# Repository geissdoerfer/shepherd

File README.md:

# SHEpHERD: SyncHronized Energy Harvesting Emulator RecorDer

DEPRECATION NOTICE:
This repository has been deprecated in favor of [the next generation of Shepherd](https://github.com/orgua/shepherd).

Batteryless sensor nodes depend on harvesting energy from their environment.
Developing solutions involving groups of batteryless nodes requires a tool to analyze, understand and replicate spatio-temporal harvesting conditions.
*shepherd* is a testbed for the batteryless Internet of Things, allowing to record harvesting conditions at multiple points in space over time.
The recorded data can be replayed to attached wireless sensor nodes, examining their behaviour under the constraints of spatio-temporal energy availability.

**Features**

 - High-speed, high resolution current and voltage sensing
 - Technology-agnostic: Currently, solar and kinetic energy harvesting are supported
 - Remote programming/debugging of ARM Cortex-M MCUs using Serial-Wire-Debug
 - High resolution, synchronized GPIO tracing
 - Configurable, constant voltage power supply for attached sensor nodes
 - Level-translated serial connection to the attached sensor nodes

For a detailed description see our [Paper](https://wwwpub.zih.tu-dresden.de/~mzimmerl/pubs/geissdoerfer19shepherd.pdf).

A *shepherd* instance consists of a group of spatially distributed *shepherd* nodes that are time-synchronized with each other.
Each *shepherd* node consists of a [BeagleBone](https://beagleboard.org/bone), the *shepherd* cape and a particular choice of capelets according to the user requirements.

This repository contains the hardware design files for the shepherd cape and the various capelets, the software running on each *shepherd* node as well as the tool to orchestrate a group of *shepherd* nodes connected to a network.

## Quickstart

Start by assembling your *shepherd* nodes, consisting of a BeagleBone Green/Black, a *shepherd* cape, a harvesting capelet and a target capelet.
The next step is to manually install the latest Ubuntu Linux on each BeagleBone.
You can install it to SD-card or the on-board EMMC flash, following [the official instructions](https://elinux.org/BeagleBoardUbuntu).
Make sure to follow the instructions for **BeagleBone**.

The following instructions describe how to install the *shepherd* software on a group of *shepherd* nodes connected to an Ethernet network.
We assume that your local machine is connected to the same network, that the nodes have internet access and that you know the IP address of each node.

If you haven't done it yet, clone this repository to your local machine:

```
git clone https://github.com/geissdoerfer/shepherd.git
```

Next, install the tools used for installing and controlling the *shepherd* nodes.
We'll use [Ansible](https://www.ansible.com/) to remotely roll out the basic configuration to each *shepherd* node and *shepherd-herd* to orchestrate recording/emulation across all nodes.
The tools are hosted on `PyPI` and require Python version >= 3.6.
You'll also need to have `sshpass` installed on your machine, which is available through the package management system of all major distributions.
Install the tools using `pip`:

```
pip3 install ansible shepherd-herd
```

The `inventory/herd.yml` file shows an example of how to provide the host names and known IP addresses of your BeagleBones.
Adjust it to reflect your setup.
You can arbitrarily choose and assign the hostnames (sheep0, sheep1, in this example) and the ansible_user (jane in this example).

```
sheep:
  hosts:
    sheep0:
        ansible_host: 192.168.1.100
    sheep1:
        ansible_host: 192.168.1.101
    sheep2:
        ansible_host: 192.168.1.102
  vars:
    ansible_user: jane
```

Now run the `bootstrap.yml` *Ansible* playbook, which sets the hostname, creates a user and enables passwordless ssh and sudo:

```
ansible-playbook deploy/bootstrap.yml
```

Finally, use the `install.yml` playbook to setup the *shepherd* software, optionally configuring PTP for time-synchronization:

```
ansible-playbook deploy/install.yml -e ptp=true
```

## Usage

Record two minutes of data:

```
shepherd-herd record -l 120 -o recording.h5
```
The command starts the recording asynchronously and returns after all nodes have started recording.
While the nodes are still recording (indicated by blinking of LED 1 and 2), prepare a directory on your local machine:

```
mkdir ~/shepherd_recordings
```

After the nodes stop blinking, you can retrieve the data to analyze it on your local machine:

```
shepherd-herd retrieve recording.h5 ~/shepherd_recordings
```

After installing some additional dependencies, you can use the provided command line utility from `extra/plot.py` to visualize the recorded data:

```
pip install numpy matplotlib h5py click
python extra/plot.py -f ~/shepherd_recordings/sheep1/rec.h5
```

For a detailed description of the [HDF5](https://en.wikipedia.org/wiki/Hierarchical_Data_Format) based data format, refer to the [corresponding documentation](https://shepherd-testbed.readthedocs.io/en/latest/user/data_format.html).

Finally, replay the previously recorded data to the attached sensor nodes, recording their power consumption:

```
shepherd-herd emulate -o consumption.h5 recording.h5
```

Try `shepherd-herd --help` or check out the documentation [here](https://shepherd-testbed.readthedocs.io/en/latest/user/cli.html#shepherd-herd) for a list of all options.

## Problems and Questions

*shepherd* is an early stage project and chances are that something is not working as expected.
Also, some features are not yet fully supported or documented.
If you experience issues or require additional features, please get in touch via e-mail or by creating an issue on github.

## Documentation

The documentation is hosted on [readthedocs](https://shepherd-testbed.readthedocs.io/en/latest/).

## People

*shepherd* development is lead at the Networked Embedded Systems Lab at TU Dresden as part of the DFG-funded project Next-IoT.

The following people have contributed to *shepherd*:

 - [Kai Geissdoerfer](https://www.researchgate.net/profile/Kai_Geissdoerfer)
 - [Mikolaj Chwalisz](https://www.tkn.tu-berlin.de/team/chwalisz/)
 - [Marco Zimmerling](https://wwwpub.zih.tu-dresden.de/~mzimmerl/)
 - [Justus Paulick](https://github.com/kugelbit)
 - [Boris Blokland](https://github.com/borro0)
 - [Ingmar Splitt](https://github.com/orgua)

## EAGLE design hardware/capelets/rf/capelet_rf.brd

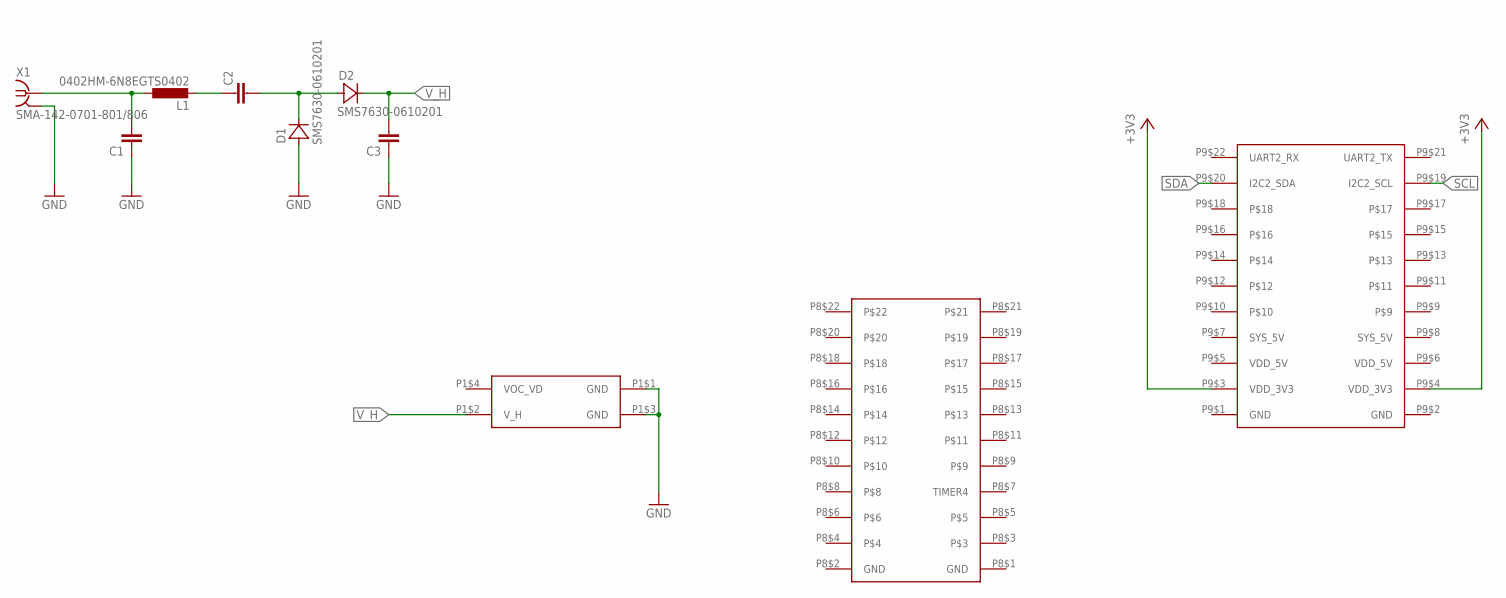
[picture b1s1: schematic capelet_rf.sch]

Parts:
C1, C2, C3: C_SMD0402; CAPC1005X55
D1, D2: SMS7630-0610201; DIOC0502X27N
L1: 0402HM-6N8EGTS0402; INDC1004X60N
X1: SMA-142-0701-801/806; J502-ND-142-0701-801/806
Y1: SHPRD_CPLT_H

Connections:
+3V3: Y1.P9$3 (VDD_3V3), Y1.P9$4 (VDD_3V3)
GND: C1.1, C3.1, D1.1 (A), X1.G@1 (2), X1.G@2 (2), X1.G@3 (2), X1.G@4 (2), Y1.P1$1 (GND), Y1.P1$3 (GND), Y1.P8$1 (GND), Y1.P8$2 (GND), Y1.P9$1 (GND), Y1.P9$2 (GND)
unnamed: C2.2, D1.2 (C), D2.1 (A)
unnamed: C1.2, L1.1, X1.1
unnamed: C2.1, L1.2
SCL: Y1.P9$19 (I2C2_SCL)
SDA: Y1.P9$20 (I2C2_SDA)
SYS_5V: Y1.P9$7 (SYS_5V), Y1.P9$8 (SYS_5V)
VDD_5V: Y1.P9$5 (VDD_5V), Y1.P9$6 (VDD_5V)
V_H: C3.2, D2.2 (C), Y1.P1$2 (V_H)

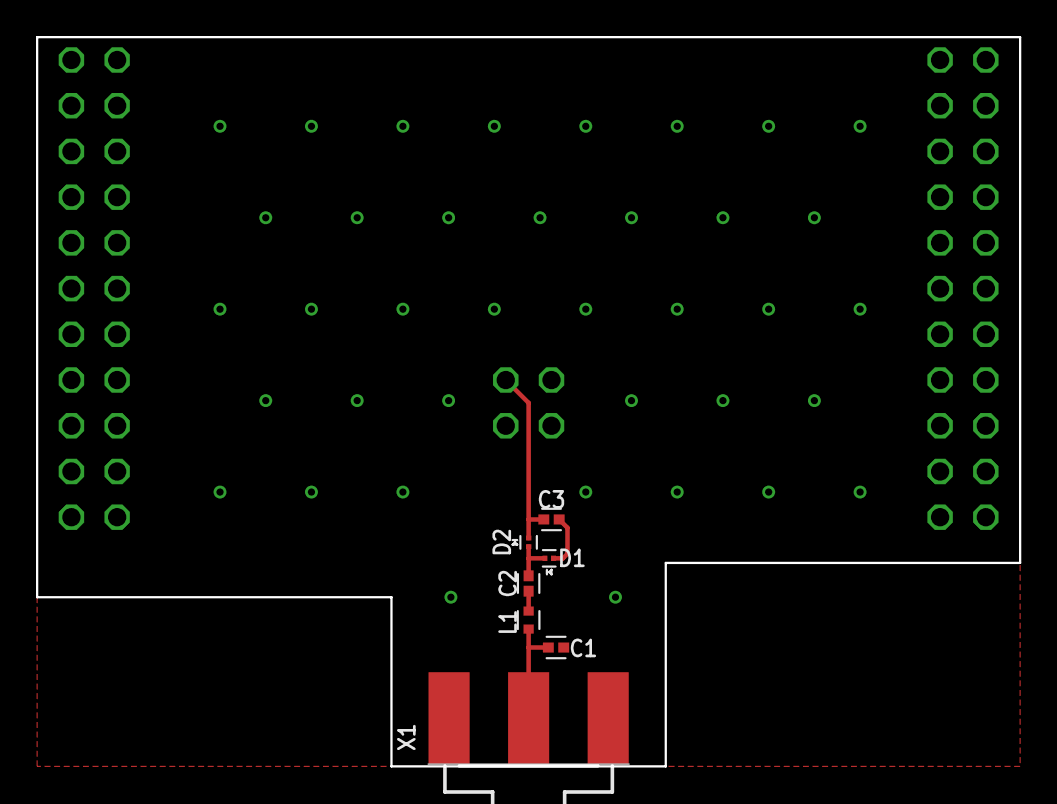
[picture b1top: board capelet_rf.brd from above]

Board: 2 copper layers, 54.6 x 40.5 mm, 8 parts (0 on the bottom side), 8 nets.

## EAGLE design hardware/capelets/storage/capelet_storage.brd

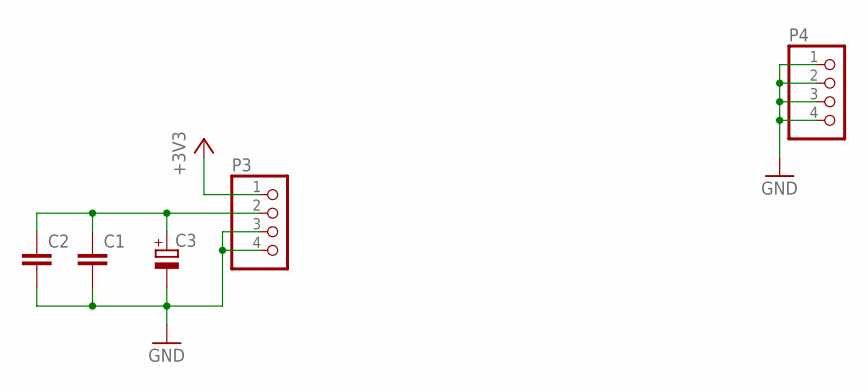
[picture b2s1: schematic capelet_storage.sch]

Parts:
C1: C_SMD0805; CAPC2012X145
C2: C_SMD1210; CAPC3225X280
C3: CPOL-EUE5-8.5; E5-8,5
P3, P4: PINHD-1X4; 1X04

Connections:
+3V3: P3.1
GND: C1.2, C2.2, C3.-, P3.3, P3.4, P4.1, P4.2, P4.3, P4.4
unnamed: C1.1, C2.1, C3.+, P3.2

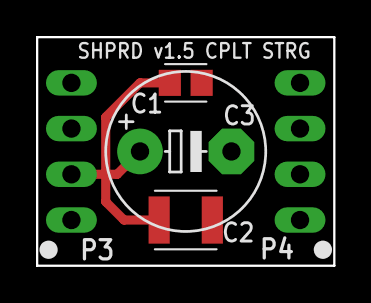
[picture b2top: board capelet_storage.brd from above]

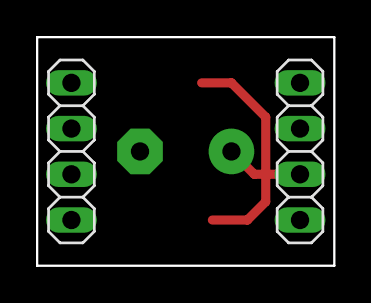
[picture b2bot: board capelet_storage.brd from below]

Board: 2 copper layers, 16.5 x 12.7 mm, 6 parts (2 on the bottom side), 2 nets.

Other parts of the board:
U$1: SHPRD_CPLT_S

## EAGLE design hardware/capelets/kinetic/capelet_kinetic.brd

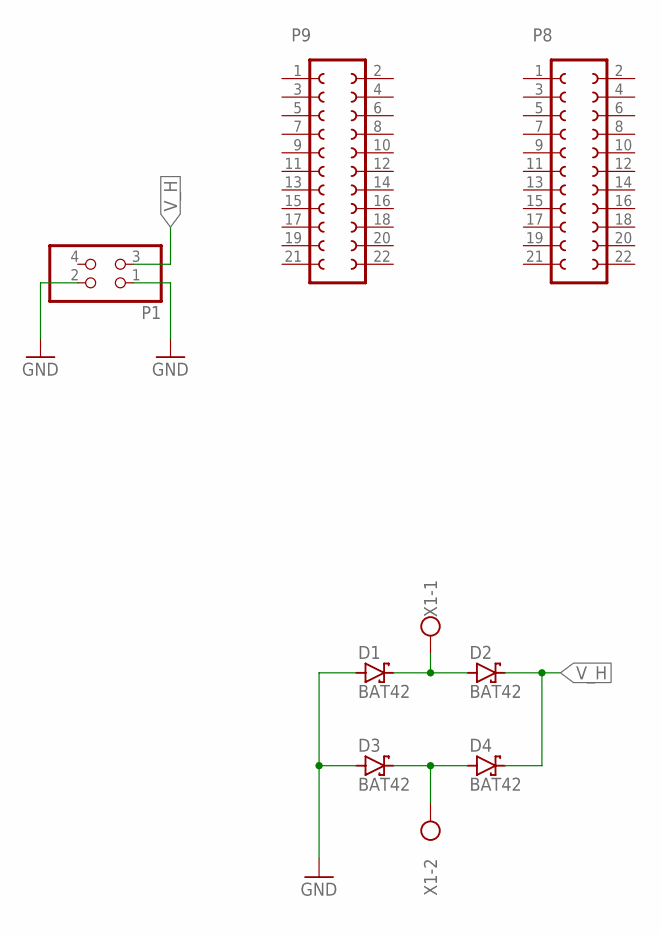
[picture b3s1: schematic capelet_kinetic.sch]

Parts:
D1, D2, D3, D4: BAT42; DO35-10
P1: PINHD-2X2; 2X02
P8, P9: FE11-2
X1: W237-102

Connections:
GND: D1.A, D3.A, P1.1, P1.2
unnamed: D1.C, D2.A, X1.1
unnamed: D3.C, D4.A, X1.2
V_H: D2.C, D4.C, P1.3

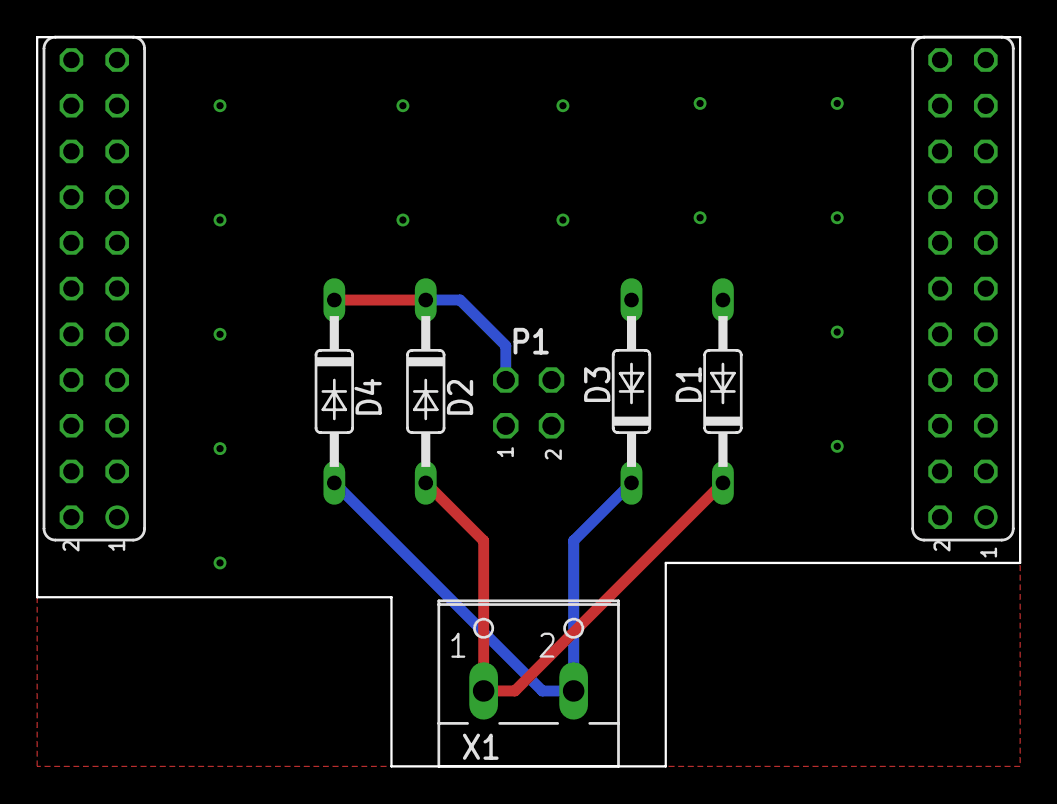
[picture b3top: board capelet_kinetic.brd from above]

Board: 2 copper layers, 54.6 x 40.5 mm, 9 parts (1 on the bottom side), 4 nets.

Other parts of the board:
U$1: SHPRD_CPLT_H

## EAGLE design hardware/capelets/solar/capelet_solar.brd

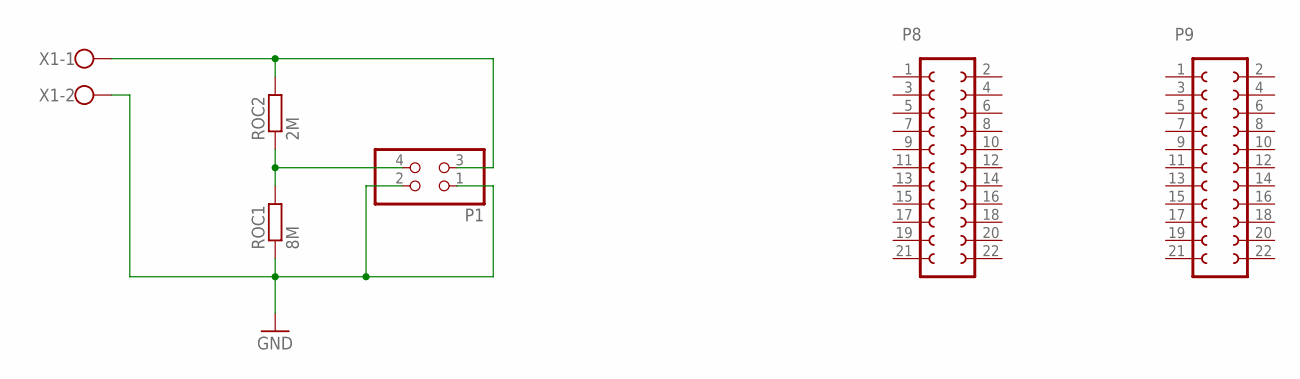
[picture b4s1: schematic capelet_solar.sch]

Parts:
P1: PINHD-2X2; 2X02
P8, P9: FE11-2
ROC1: 8M; RESC2012X65
ROC2: 2M; RESC2012X65
X1: W237-102

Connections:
GND: P1.1, P1.2, ROC1.1, X1.2
unnamed: P1.3, ROC2.2, X1.1
unnamed: P1.4, ROC1.2, ROC2.1

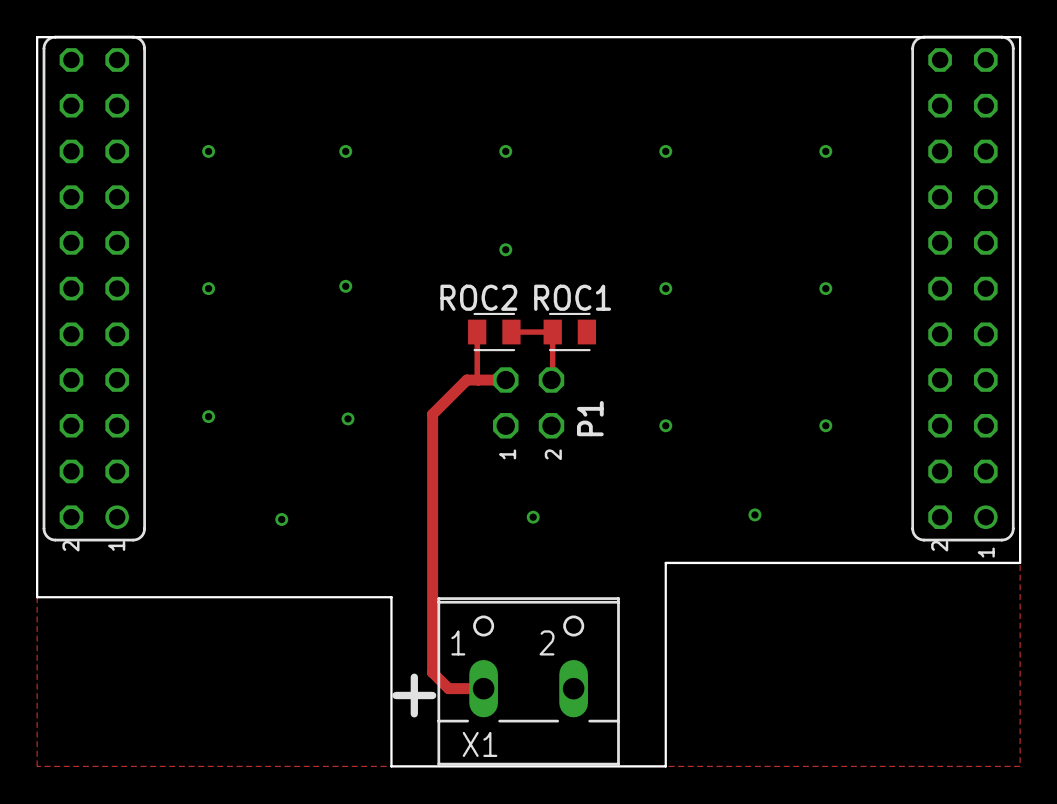
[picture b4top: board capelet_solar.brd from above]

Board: 2 copper layers, 54.6 x 40.5 mm, 7 parts (1 on the bottom side), 3 nets.

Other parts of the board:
U$1: SHPRD_CPLT_H

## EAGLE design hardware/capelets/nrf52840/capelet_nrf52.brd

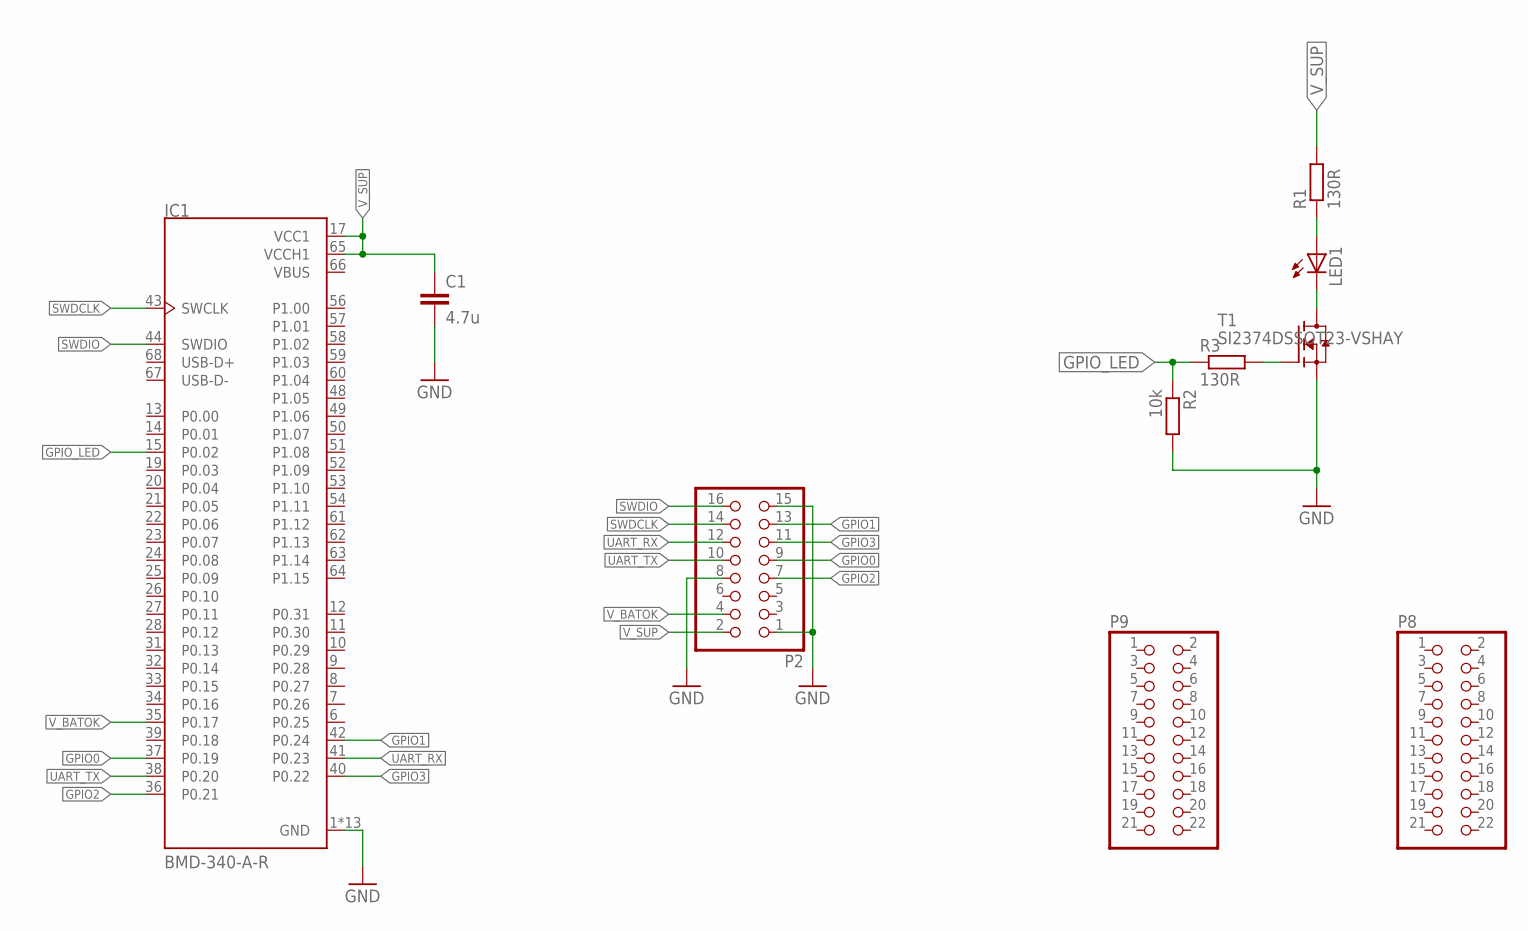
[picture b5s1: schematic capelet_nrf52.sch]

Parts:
C1: 4.7u; CAPC1608X95
IC1: BMD-340-A-R; RIGADO_BMD-340-A-R
LED1: 598-8130-107FLED_0805; LEDC2012X75
P2: PINHD-2X8; 2X08
P8, P9: PINHD-2X11; 2X11
R1, R3: 130R; RESC2012X65
R2: 10k; RESC2012X65
T1: SI2374DSSOT23-VSHAY; SOT95P237X112-3

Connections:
GND: C1.2, IC1.1 (GND), IC1.2 (GND), IC1.3 (GND), IC1.4 (GND), IC1.5 (GND), IC1.16 (GND), IC1.18 (GND), IC1.29 (GND), IC1.30 (GND), IC1.45 (GND), IC1.46 (GND), IC1.47 (GND), IC1.55 (GND), P2.1, P2.8, P2.15, R2.2, T1.2 (S)
GPIO0: IC1.37 (P0.19), P2.9
GPIO1: IC1.42 (P0.24), P2.13
GPIO2: IC1.36 (P0.21), P2.7
GPIO3: IC1.40 (P0.22), P2.11
GPIO_LED: IC1.15 (P0.02), R2.1, R3.1
unnamed: R3.2, T1.1 (G)
unnamed: LED1.1 (C), T1.3 (D)
unnamed: LED1.2 (A), R1.1
SWDCLK: IC1.43 (SWCLK), P2.14
SWDIO: IC1.44 (SWDIO), P2.16
UART_RX: IC1.41 (P0.23), P2.12
UART_TX: IC1.38 (P0.20), P2.10
VBUS: IC1.66 (VBUS)
V_BATOK: IC1.35 (P0.17), P2.4
V_SUP: C1.1, IC1.17 (VCC1), IC1.65 (VCCH1), P2.2, R1.2

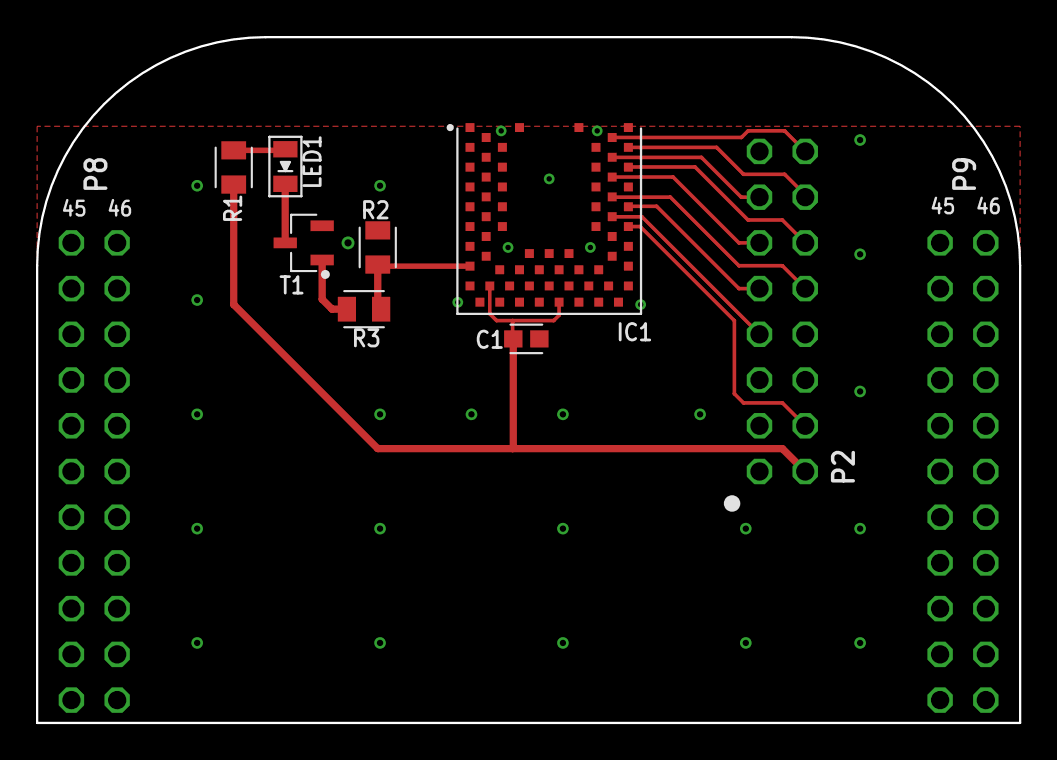
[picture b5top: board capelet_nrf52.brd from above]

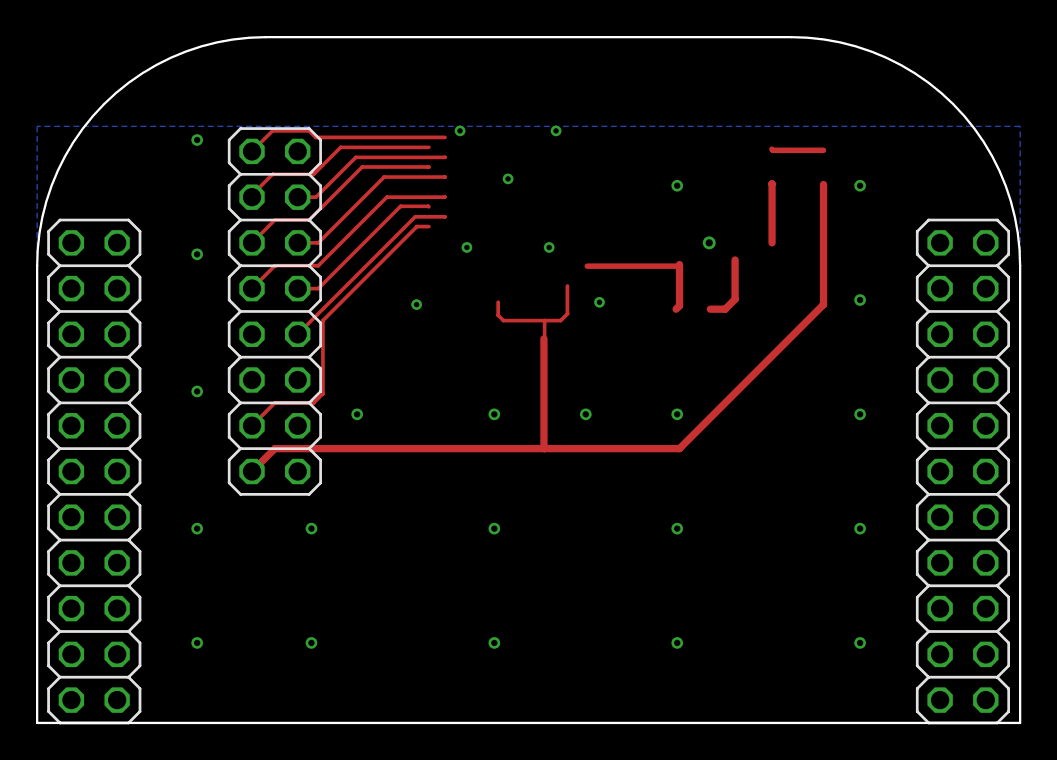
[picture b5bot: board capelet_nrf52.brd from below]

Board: 2 copper layers, 54.6 x 38.1 mm, 11 parts (3 on the bottom side), 15 nets.

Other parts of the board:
U$3: SHPRD_CPLT_T

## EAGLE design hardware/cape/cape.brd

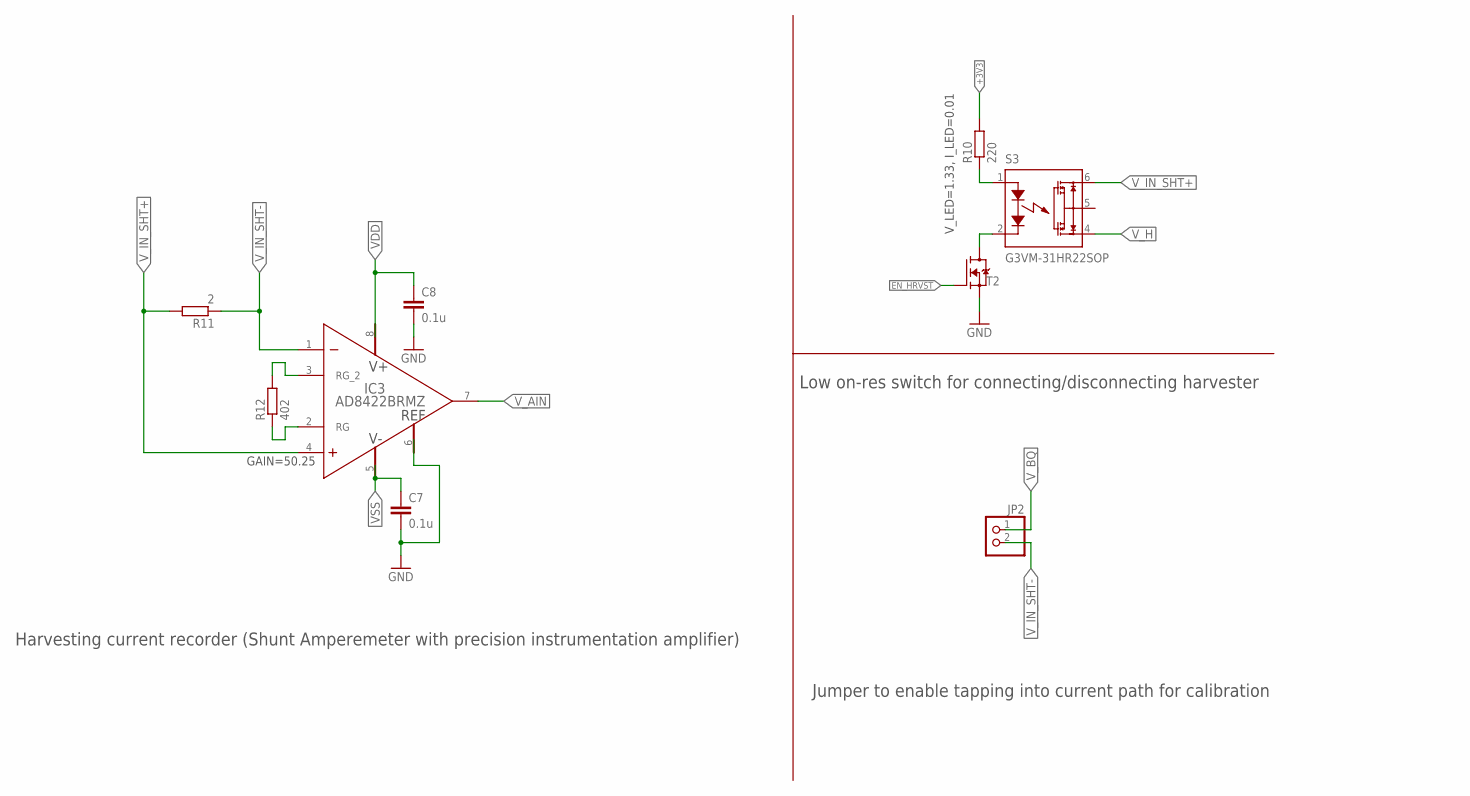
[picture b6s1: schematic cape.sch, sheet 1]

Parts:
C7, C8: 0.1u; CAPC1005X55
IC3: AD8422BRMZ; RM_8-L
JP2: PINHD-1X2; 1X02
R10: 220; RESC1608X55
R11: 2; RESC1608X55
R12: 402; RESC1608X55
S3: G3VM-31HR22SOP; SOP06
T2: SI2374DSSOT23-VSHAY; SOT95P237X112-3

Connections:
+3V3: R10.2; also elsewhere on the board
EN_HRVST: T2.1 (G); also elsewhere on the board
GND: C7.2, C8.2, IC3.6 (REF), T2.2 (S); also elsewhere on the board
unnamed: R10.1, S3.1 (A)
unnamed: IC3.3 (RG_2), R12.2
unnamed: IC3.2 (RG), R12.1
unnamed: S3.2 (K), T2.3 (D)
VDD: C8.1, IC3.8 (V+); also elsewhere on the board
VSS: C7.1, IC3.5 (V-); also elsewhere on the board
V_AIN: IC3.7 (OUT); also elsewhere on the board
V_BQ: JP2.1; also elsewhere on the board
V_H: S3.4 (D2); also elsewhere on the board
V_IN_SHT+: IC3.4 (IN+), R11.2, S3.6 (D1); also elsewhere on the board
V_IN_SHT-: IC3.1 (IN-), JP2.2, R11.1; also elsewhere on the board

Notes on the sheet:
V_LED=1.33, I_LED=0.01
GAIN=50.25
Harvesting current recorder (Shunt Amperemeter with precision instrumentation amplifier)
Low on-res switch for connecting/disconnecting harvester
Jumper to enable tapping into current path for calibration

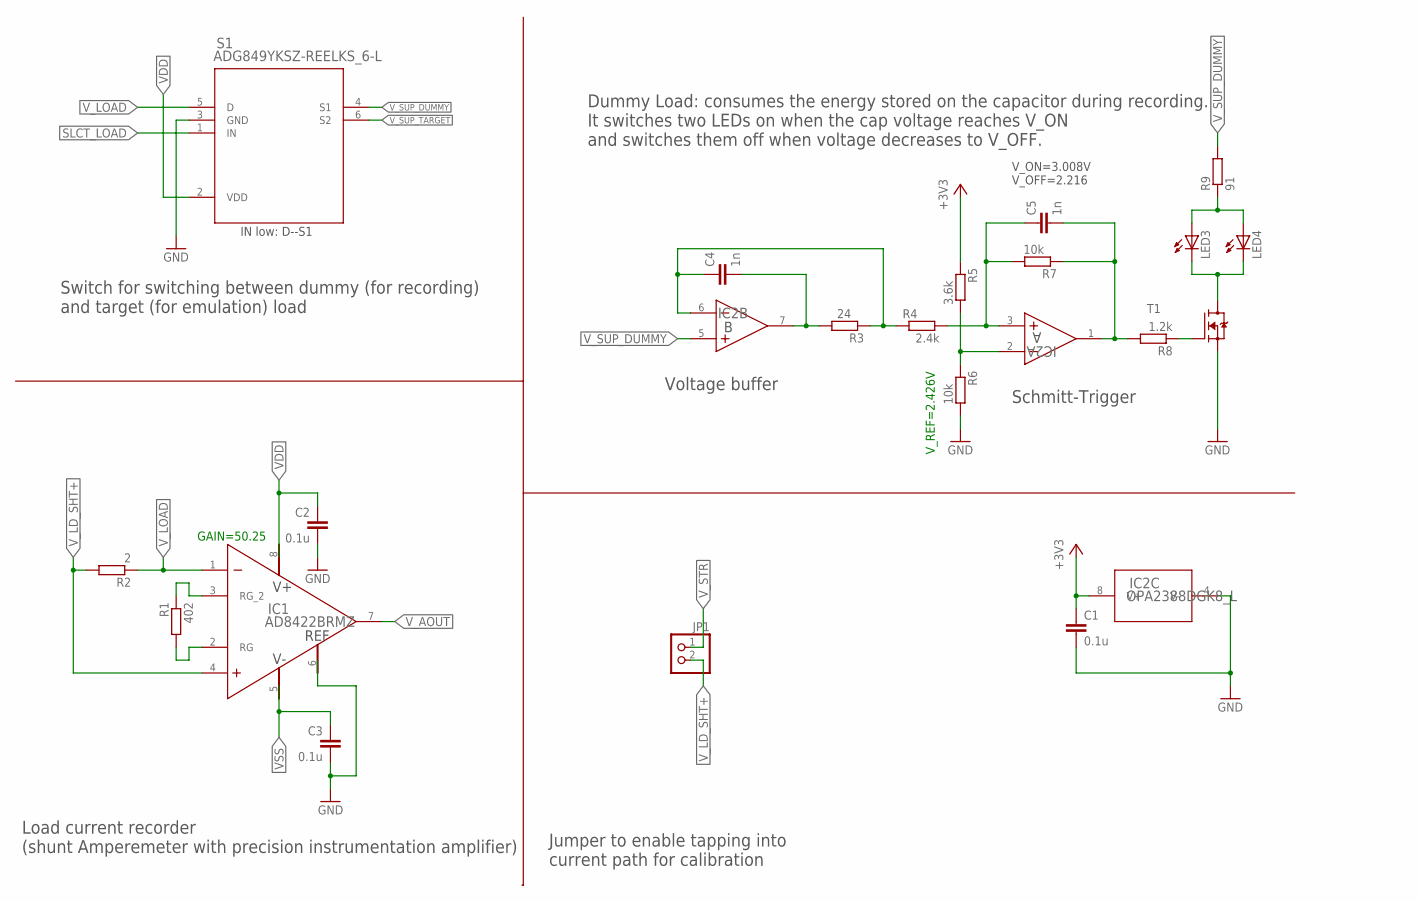
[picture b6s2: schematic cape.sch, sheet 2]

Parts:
C1, C2, C3: 0.1u; CAPC1005X55
C4, C5: 1n; CAPC1005X55
IC1: AD8422BRMZ; RM_8-L
IC2: OPA2388DGK8_L; DGK8-L
JP1: PINHD-1X2; 1X02
LED3, LED4: 598-8130-107FLED_0805; LEDC2012X75
R1: 402; RESC1608X55
R2: 2; RESC1608X55
R3: 24; RESC1005X40
R4: 2.4k; RESC1005X40
R5: 3.6k; RESC1005X40
R6, R7: 10k; RESC1005X40
R8: 1.2k; RESC1005X40
R9: 91; RESC1608X55
S1: ADG849YKSZ-REELKS_6-L; KS_6-L
T1: SI2374DSSOT23-VSHAY; SOT95P237X112-3

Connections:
+3V3: C1.1, IC2.8 (V+), R5.1; also elsewhere on the board
GND: C1.2, C2.2, C3.2, IC1.6 (REF), IC2.4 (V-), R6.2, S1.3 (GND), T1.2 (S); also elsewhere on the board
unnamed: R8.1, T1.1 (G)
unnamed: LED3.2 (A), LED4.2 (A), R9.1
unnamed: C5.2, IC2.1 (OUT), R7.1, R8.2
unnamed: LED3.1 (C), LED4.1 (C), T1.3 (D)
unnamed: C5.1, IC2.3 (IN+), R4.2, R7.2
unnamed: IC2.2 (IN-), R5.2, R6.1
unnamed: C4.1, IC2.6 (IN-), R3.1, R4.1
unnamed: C4.2, IC2.7 (OUT), R3.2
unnamed: IC1.2 (RG), R1.2
unnamed: IC1.3 (RG_2), R1.1
SLCT_LOAD: S1.1 (IN); also elsewhere on the board
VDD: C2.1, IC1.8 (V+), S1.2 (VDD); also elsewhere on the board
VSS: C3.1, IC1.5 (V-); also elsewhere on the board
V_AOUT: IC1.7 (OUT); also elsewhere on the board
V_LD_SHT+: IC1.4 (IN+), JP1.2, R2.2; also elsewhere on the board
V_LOAD: IC1.1 (IN-), R2.1, S1.5 (D); also elsewhere on the board
V_STR: JP1.1; also elsewhere on the board
V_SUP_DUMMY: IC2.5 (IN+), R9.2, S1.4 (S1)
V_SUP_TARGET: S1.6 (S2); also elsewhere on the board

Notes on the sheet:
IN low: D--S1
GAIN=50.25
V_REF=2.426V
V_ON=3.008V V_OFF=2.216
Dummy Load: consumes the energy stored on the capacitor during recording. It switches two LEDs on when the cap voltage reaches V_ON and switches them off when voltage decreases to V_OFF.
Voltage buffer
Schmitt-Trigger
Switch for switching between dummy (for recording) and target (for emulation) load
Load current recorder (shunt Amperemeter with precision instrumentation amplifier)
Jumper to enable tapping into current path for calibration

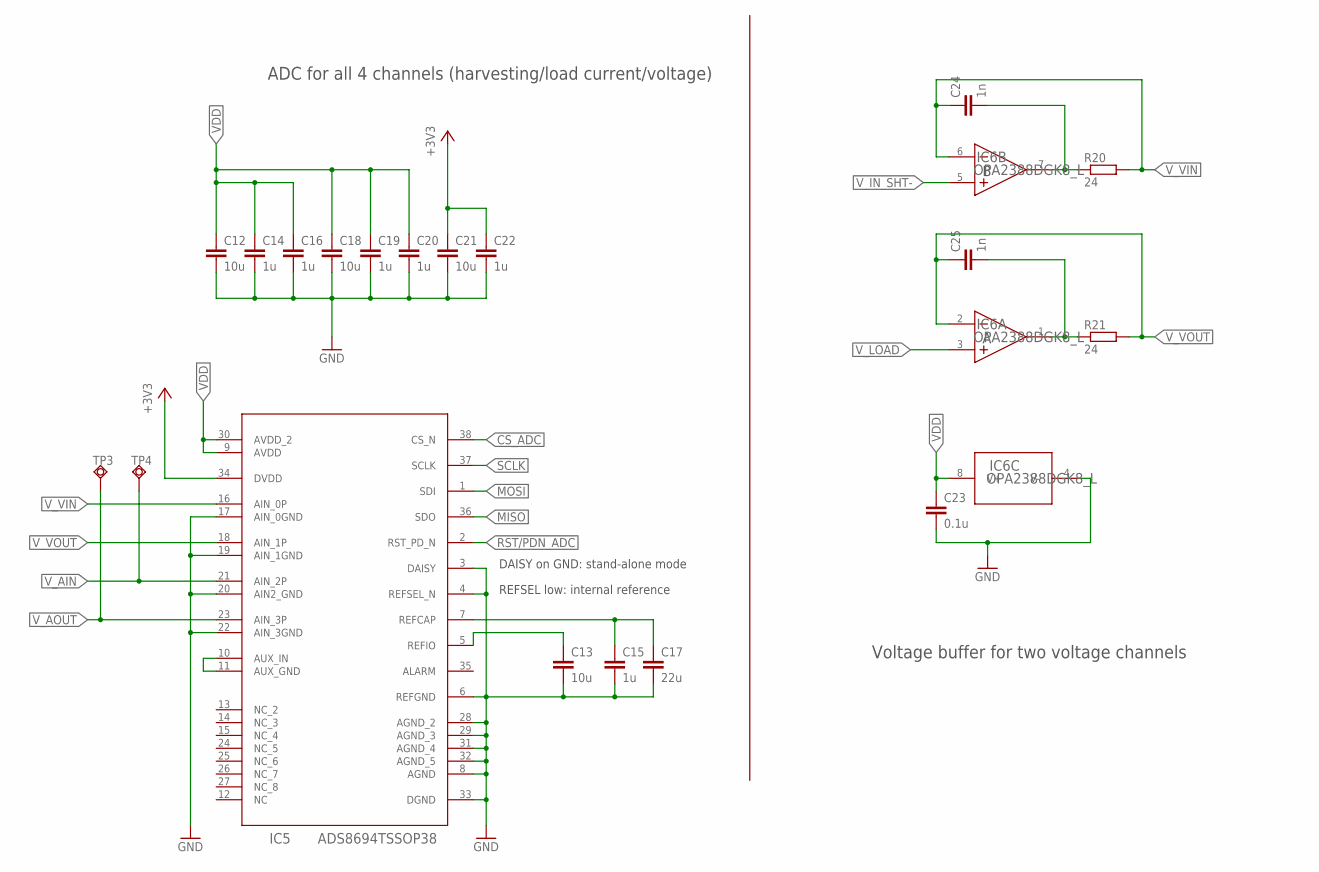
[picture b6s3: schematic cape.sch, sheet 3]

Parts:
C12, C13, C18, C21: 10u; CAPC2012X145
C14, C15, C16, C19, C20, C22: 1u; CAPC1608X95
C17: 22u; CAPC3225X280
C23: 0.1u; CAPC1005X55
C24, C25: 1n; CAPC1005X55
IC5: ADS8694TSSOP38; TSSOP38
IC6: OPA2388DGK8_L; DGK8-L
R20, R21: 24; RESC1005X40
TP3, TP4: TPSQTP06R; TP06R

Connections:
+3V3: C21.1, C22.1, IC5.34 (DVDD); also elsewhere on the board
CS_ADC: IC5.38 (CS_N); also elsewhere on the board
GND: C12.2, C13.2, C14.2, C15.2, C16.2, C17.2, C18.2, C19.2, C20.2, C21.2, C22.2, C23.2, IC5.3 (DAISY), IC5.4 (REFSEL_N), IC5.6 (REFGND), IC5.8 (AGND), IC5.17 (AIN_0GND), IC5.19 (AIN_1GND), IC5.20 (AIN2_GND), IC5.22 (AIN_3GND), IC5.28 (AGND_2), IC5.29 (AGND_3), IC5.31 (AGND_4), IC5.32 (AGND_5), IC5.33 (DGND), IC6.4 (V-); also elsewhere on the board
MISO: IC5.36 (SDO); also elsewhere on the board
MOSI: IC5.1 (SDI); also elsewhere on the board
unnamed: C13.1, IC5.5 (REFIO)
unnamed: C15.1, C17.1, IC5.7 (REFCAP)
unnamed: IC5.10 (AUX_IN), IC5.11 (AUX_GND)
unnamed: C25.2, IC6.1 (OUT), R21.1
unnamed: C24.2, IC6.7 (OUT), R20.1
RST/PDN_ADC: IC5.2 (RST_PD_N); also elsewhere on the board
SCLK: IC5.37 (SCLK); also elsewhere on the board
VDD: C12.1, C14.1, C16.1, C18.1, C19.1, C20.1, C23.1, IC5.9 (AVDD), IC5.30 (AVDD_2), IC6.8 (V+); also elsewhere on the board
V_AIN: IC5.21 (AIN_2P), TP4.TP; also elsewhere on the board
V_AOUT: IC5.23 (AIN_3P), TP3.TP; also elsewhere on the board
V_IN_SHT-: IC6.5 (IN+); also elsewhere on the board
V_LOAD: IC6.3 (IN+); also elsewhere on the board
V_VIN: C24.1, IC5.16 (AIN_0P), IC6.6 (IN-), R20.2
V_VOUT: C25.1, IC5.18 (AIN_1P), IC6.2 (IN-), R21.2

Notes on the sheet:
REFSEL low: internal reference
DAISY on GND: stand-alone mode
ADC for all 4 channels (harvesting/load current/voltage)
Voltage buffer for two voltage channels

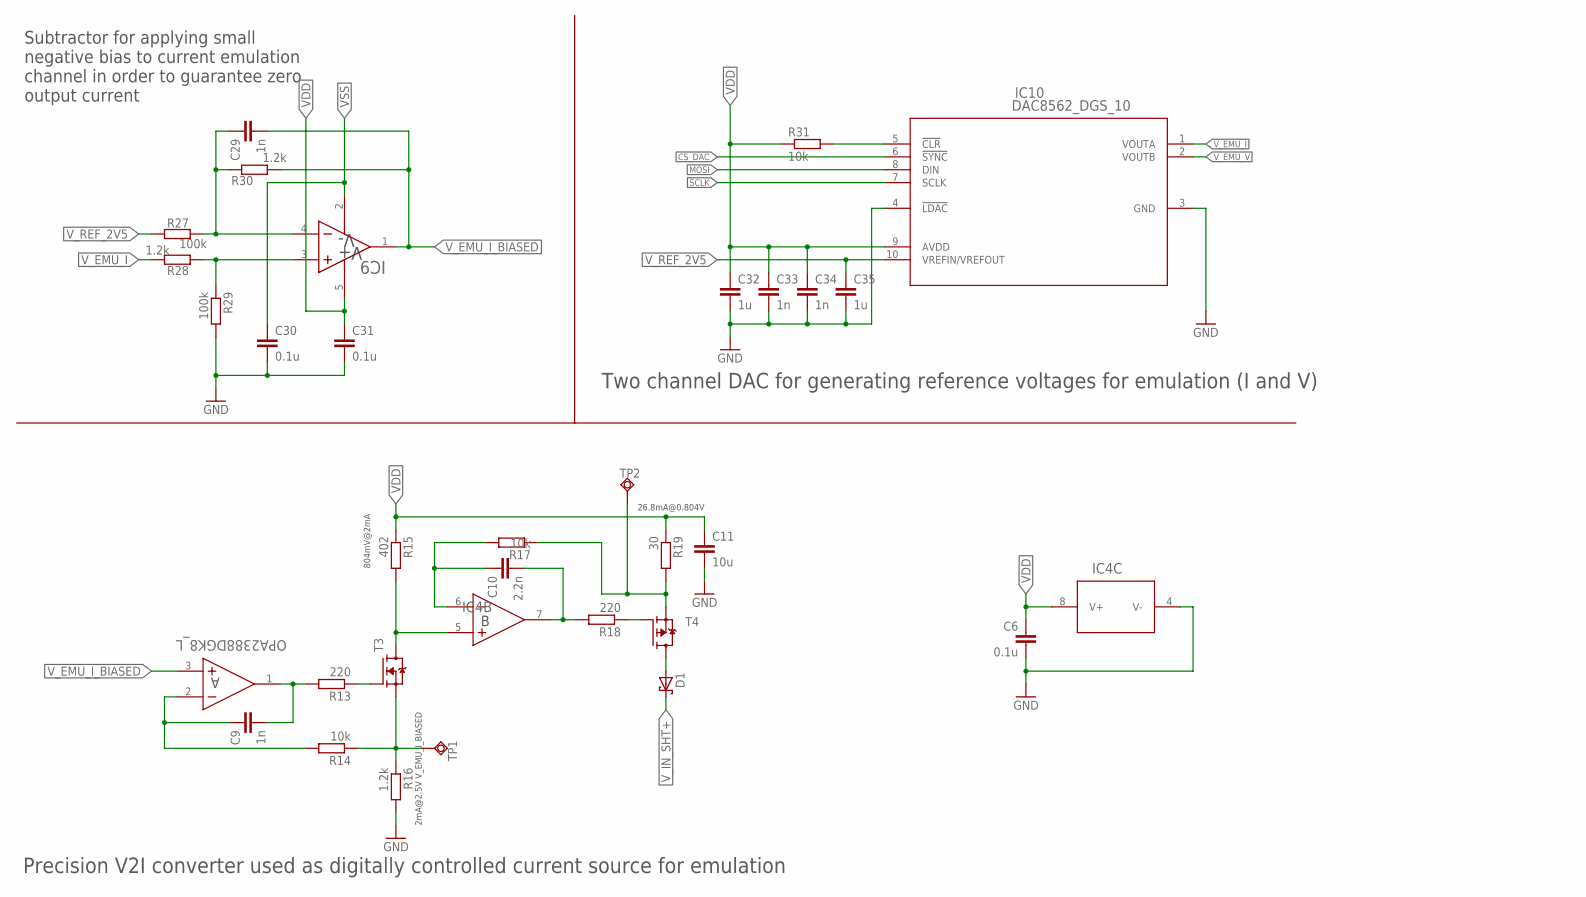
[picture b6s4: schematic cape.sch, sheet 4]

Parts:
C6, C30, C31: 0.1u; CAPC1005X55
C9, C29, C33, C34: 1n; CAPC1005X55
C10: 2.2n; CAPC1005X55
C11: 10u; CAPC2012X145
C32, C35: 1u; CAPC1608X95
D1: BAT43WS-HE3SOD-323; SOD2513X110
IC4: OPA2388DGK8_L; DGK8-L
IC9: LMP7701MF; DBV5-L
IC10: DAC8562_DGS_10; DGS10
R13, R18: 220; RESC1608X55
R14, R17, R31: 10k; RESC1005X40
R15: 402; RESC1608X55
R16, R28, R30: 1.2k; RESC1005X40
R19: 30; RESC1005X40
R27, R29: 100k; RESC1005X40
T3: SI2374DSSOT23-VSHAY; SOT95P237X112-3
T4: SI2307SOT23-VSHAY; SOT95P237X112-3
TP1, TP2: TPSQTP06R; TP06R

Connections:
CS_DAC: IC10.6 (!SYNC); also elsewhere on the board
GND: C6.2, C11.2, C30.2, C31.2, C32.2, C33.2, C34.2, C35.2, IC4.4 (V-), IC10.3 (GND), IC10.4 (!LDAC), R16.2, R29.2; also elsewhere on the board
MOSI: IC10.8 (DIN); also elsewhere on the board
unnamed: C9.2, IC4.1 (OUT), R13.2
unnamed: C9.1, IC4.2 (IN-), R14.2
unnamed: IC10.5 (!CLR), R31.2
unnamed: D1.2 (A), T4.3 (D)
unnamed: C29.1, IC9.4 (IN-), R27.1, R30.2
unnamed: IC9.3 (IN+), R28.1, R29.1
unnamed: R13.1, T3.1 (G)
unnamed: R14.1, R16.1, T3.2 (S), TP1.TP
unnamed: IC4.5 (IN+), R15.2, T3.3 (D)
unnamed: C10.1, IC4.6 (IN-), R17.2
unnamed: C10.2, IC4.7 (OUT), R18.2
unnamed: R18.1, T4.1 (G)
unnamed: R17.1, R19.2, T4.2 (S), TP2.TP
SCLK: IC10.7 (SCLK); also elsewhere on the board
VDD: C6.1, C11.1, C31.1, C32.1, C33.1, C34.1, IC4.8 (V+), IC9.5 (V+), IC10.9 (AVDD), R15.1, R19.1, R31.1; also elsewhere on the board
VSS: C30.1, IC9.2 (V-); also elsewhere on the board
V_EMU_I: IC10.1 (VOUTA), R28.2
V_EMU_I_BIASED: C29.2, IC4.3 (IN+), IC9.1 (OUT), R30.1
V_EMU_V: IC10.2 (VOUTB); also elsewhere on the board
V_IN_SHT+: D1.1 (C); also elsewhere on the board
V_REF_2V5: C35.1, IC10.10 (VREFIN/VREFOUT), R27.2

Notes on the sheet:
Two channel DAC for generating reference voltages for emulation (I and V)
Subtractor for applying small negative bias to current emulation channel in order to guarantee zero output current
2mA@2.5V V_EMU_I_BIASED
804mV@2mA
26.8mA@0.804V
Precision V2I converter used as digitally controlled current source for emulation

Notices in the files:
software/python-package/shepherd/shepherd_io.py:
:copyright: (c) 2019 Networked Embedded Systems Lab, TU Dresden.
:license: MIT, see LICENSE for more details.
